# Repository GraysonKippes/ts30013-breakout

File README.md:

# TS30013 Breakout Board
This is a breakout board for the TS30013 switching voltage regulator, produced by Semtech Corporation.
This board takes in from 4.5VDC to 18VDC input and puts out 3.3VDC; additionally, it can supply up to 3A of current.
This board provides several male and female pins, as well as a screw terminal block, through which to access the power output.

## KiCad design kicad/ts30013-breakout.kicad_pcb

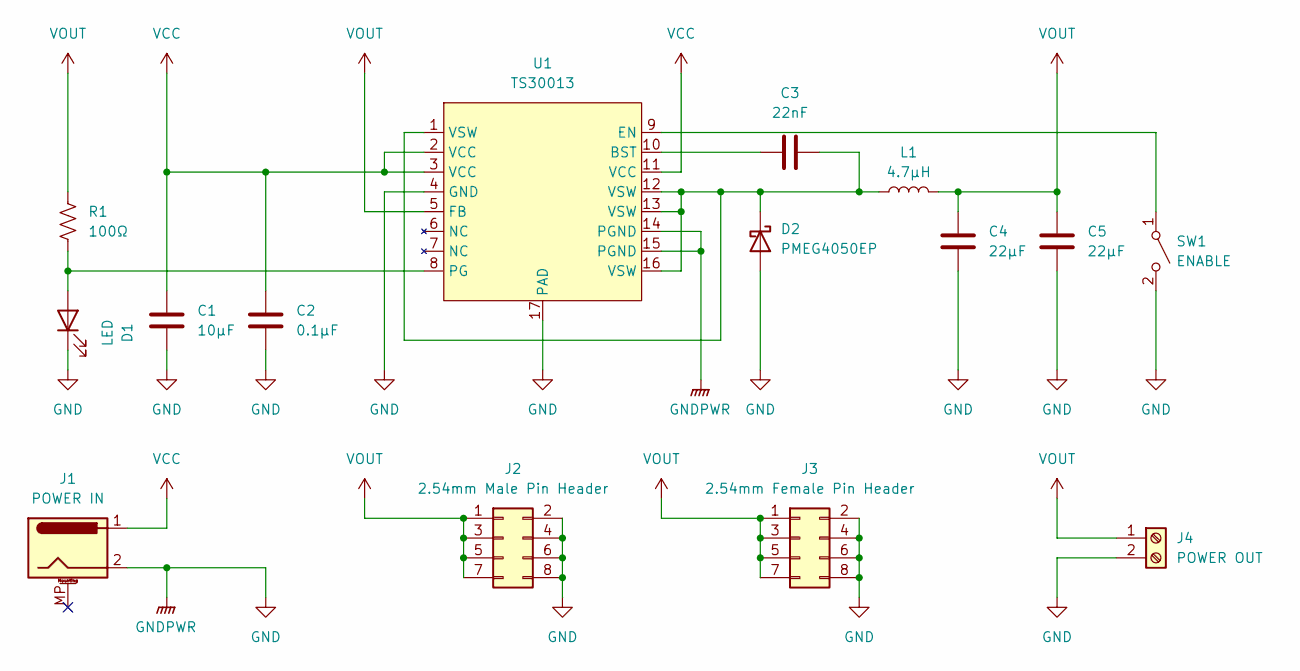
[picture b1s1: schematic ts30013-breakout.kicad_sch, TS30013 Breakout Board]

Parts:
C1: 10μF; C_1206_3216Metric_Pad1.33x1.80mm_HandSolder; LCSC Part # C13585
C2: 0.1μF; C_1206_3216Metric_Pad1.33x1.80mm_HandSolder; LCSC Part # C24497
C3: 22nF; C_1206_3216Metric_Pad1.33x1.80mm_HandSolder
C4, C5: 22μF; C_1206_3216Metric_Pad1.33x1.80mm_HandSolder; LCSC Part # C12891
D1: LED; LED_1206_3216Metric_Pad1.42x1.75mm_HandSolder
D2: PMEG4050EP; D_SOD-123F; LCSC Part # C96235
J1: POWER IN; CUI_PJ-202AH
J2: 2.54mm Male Pin Header; PinHeader_2x04_P2.54mm_Vertical
J3: 2.54mm Female Pin Header; PinSocket_2x04_P2.54mm_Vertical
J4: POWER OUT; TerminalBlock_Phoenix_PT-1,5-2-5.0-H_1x02_P5.00mm_Horizontal
L1: 4.7μH; L_Wurth_WE_PD_7345; LCSC Part # C5913310
R1: 100Ω; R_1206_3216Metric_Pad1.30x1.75mm_HandSolder
SW1: ENABLE; EG1218
U1: TS30013; QFN-16-1EP_3x3mm_P0.5mm_EP1.7x1.7mm; LCSC Part # C2650321

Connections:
GND: C1.2, C2.2, C4.2, C5.2, D1.1 (K), D2.2 (A), J1.2, J2.2, J2.4, J2.6, J2.8, J3.2, J3.4, J3.6, J3.8, J4.2, SW1.2 (B), U1.4 (GND), U1.14 (PGND), U1.15 (PGND), U1.17 (PAD)
unnamed: D1.2 (A), R1.2, U1.8 (PG)
unnamed: C3.2, D2.1 (K), L1.1, U1.1 (VSW), U1.12 (VSW), U1.13 (VSW), U1.16 (VSW)
unnamed: SW1.1 (A), U1.9 (EN)
unnamed: C3.1, U1.10 (BST)
VCC: C1.1, C2.1, J1.1, U1.2 (VCC), U1.3 (VCC), U1.11 (VCC)
VOUT: C4.1, C5.1, J2.1, J2.3, J2.5, J2.7, J3.1, J3.3, J3.5, J3.7, J4.1, L1.2, R1.1, U1.5 (FB)

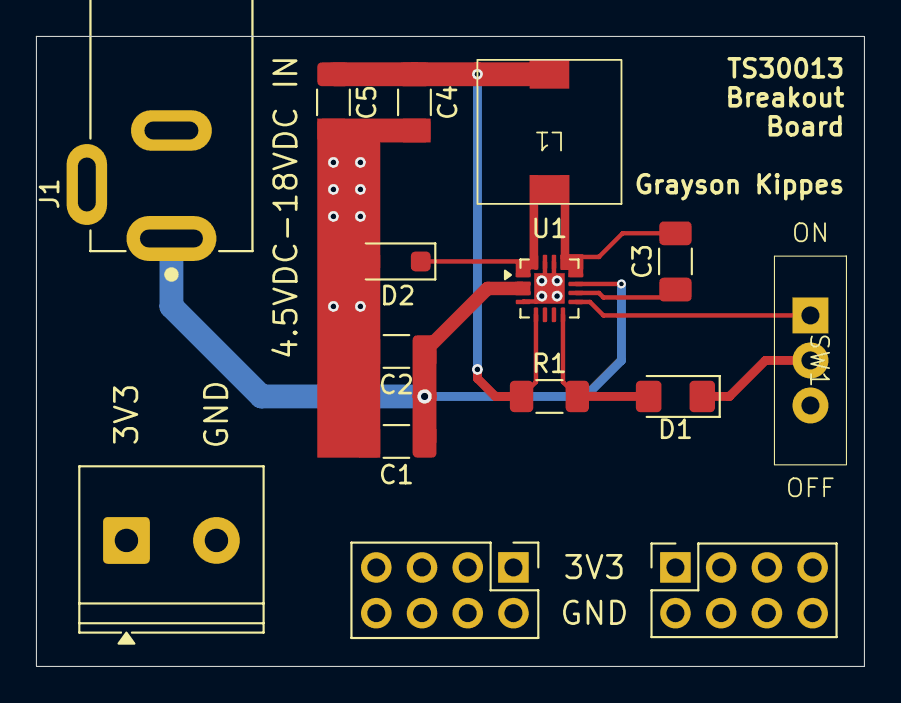
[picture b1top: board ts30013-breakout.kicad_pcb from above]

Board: 4 copper layers, 46.0 x 35.0 mm, 15 parts (0 on the bottom side), 7 nets.
